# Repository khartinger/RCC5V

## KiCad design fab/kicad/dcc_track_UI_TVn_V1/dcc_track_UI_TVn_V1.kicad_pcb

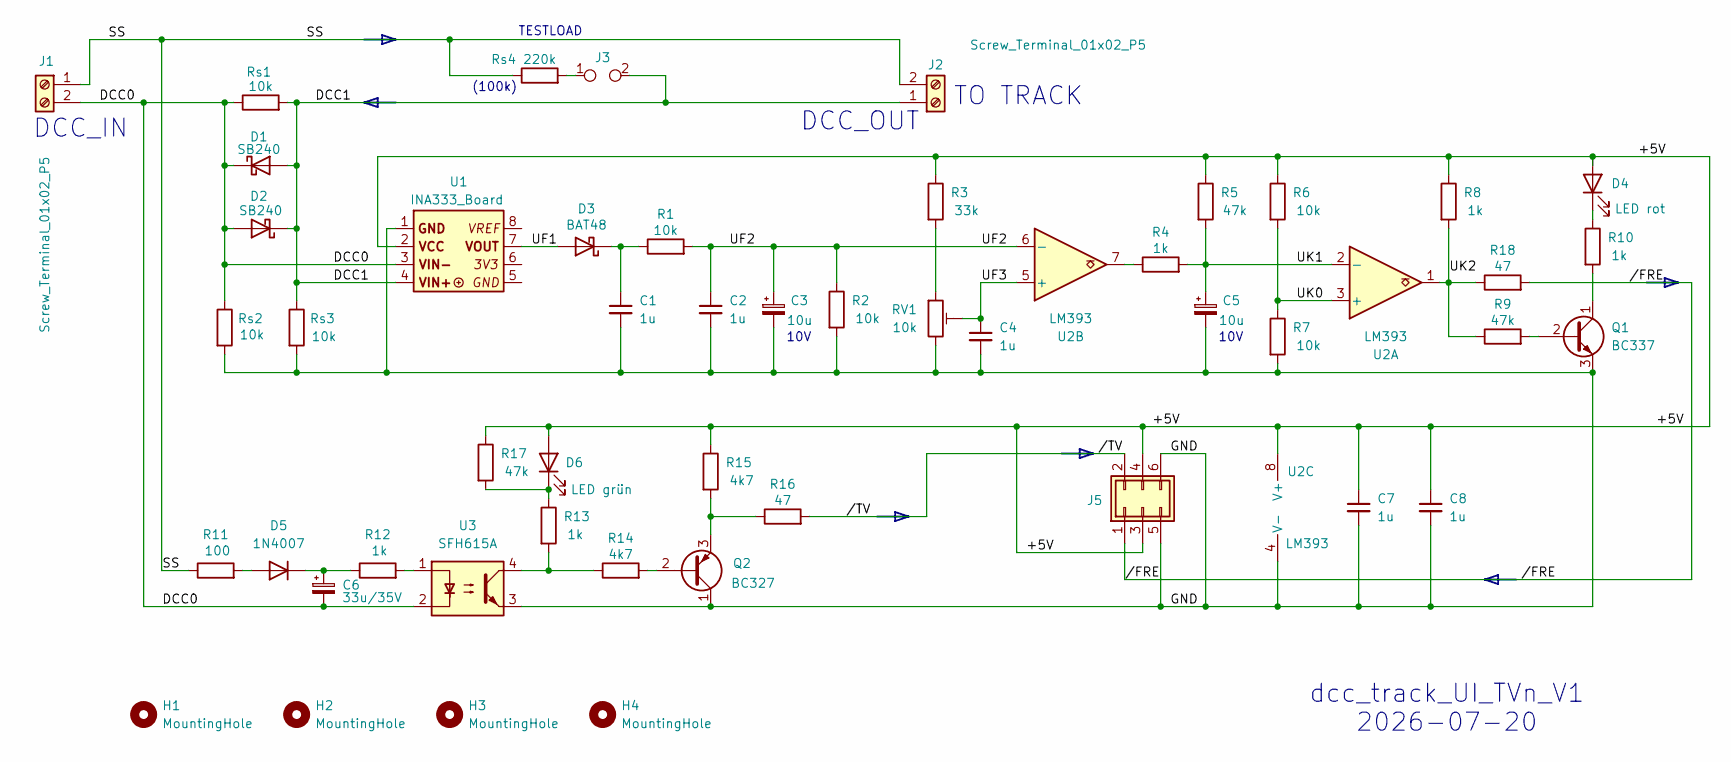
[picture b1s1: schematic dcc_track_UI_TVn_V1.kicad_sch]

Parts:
C1, C2, C4, C7, C8: 1u; C_L4mm_D3mm_P2.54mm_kh
C3, C5: 10u; ELKO_L4.32mm_D3.81mm_P2.54mm_kh
C6: 33u/35V; CP_Radial_D8.0mm_P2.50mm
D1, D2: SB240; D_DO-15_P3.81mm_Vertical_AnodeUp
D3: BAT48; D_DO-35_SOD27_P5.08mm_Horizontal_kh
D4: LED rot; LED_D3.0mm
D5: 1N4007; D_DO-41_SOD81_P3.81mm_Vertical_AnodeUp_kh
D6: LED grün; LED_D3.0mm
H1, H2, H3, H4: MountingHole; MountingHole_2.2mm_M2_Pad_TopBottom_kh
J1, J2: Screw_Terminal_01x02_P5
J3: Jumper_2; PinSocket_1x02_P2.54mm_Vertical_kh
J5: Box_02x03_P2.54_Vertical; Box_02x03_P2.54mm_Vertical_kh
Q1: BC337; TO-92_Inline_Wide_custom
Q2: BC327; TO-92_Inline_Wide_custom
R1: 10k; R_Axial_DIN0204_L3.6mm_D1.6mm_P7.62mm_Horizontal
R2, R6, R7: 10k; R_Axial_DIN0204_L3.6mm_D1.6mm_P2.54mm_Vertical_kh
R3: 33k; R_Axial_DIN0204_L3.6mm_D1.6mm_P2.54mm_Vertical_kh
R4, R8, R10, R12, R13: 1k; R_Axial_DIN0204_L3.6mm_D1.6mm_P2.54mm_Vertical_kh
R5: 47k; R_Axial_DIN0204_L3.6mm_D1.6mm_P7.62mm_Horizontal
R9, R17: 47k; R_Axial_DIN0204_L3.6mm_D1.6mm_P2.54mm_Vertical_kh
R11: 100; R_Axial_DIN0204_L3.6mm_D1.6mm_P2.54mm_Vertical
R14, R15: 4k7; R_Axial_DIN0204_L3.6mm_D1.6mm_P2.54mm_Vertical_kh
R16, R18: 47; R_Axial_DIN0204_L3.6mm_D1.6mm_P2.54mm_Vertical_kh
RV1: 10k; Trim_Bourns_3296W_Vertical
Rs1: 10k; R_Axial_DIN0204_L3.6mm_D1.6mm_P2.54mm_Vertical_kh
Rs2, Rs3: 10k; R_Axial_DIN0204_L3.6mm_D1.6mm_P7.62mm_Horizontal
Rs4: 220k; R_Axial_DIN0204_L3.6mm_D1.6mm_P7.62mm_Horizontal
U1: INA333_Board
U2: LM393; DIP-8_W7.62mm_Socket_LongPads
U3: SFH615A; DIP-4_W7.62mm

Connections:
/+5V: C7.1, C8.1, D4.2 (A), D6.2 (A), J5.3, J5.4, R3.1, R5.1, R6.1, R8.1, R15.1, R17.1, U1.2 (3A), U2.8 (V+)
/DCC0: C6.2, D1.1 (K), D2.2 (A), J1.2, Rs1.1, Rs2.1, U1.3, U3.2
/DCC1: D1.2 (A), D2.1 (K), J2.1, J3.2, Rs1.2, Rs3.1, U1.4 (PIN_4)
/GND: C1.2, C2.2, C3.2, C4.2, C5.2, C7.2, C8.2, J5.5, J5.6, Q1.3 (E), Q2.1 (C), R2.2, R7.2, RV1.3, Rs2.2, Rs3.2, U1.1, U2.4 (V-), U3.3
/SS: J1.1, J2.2, R11.1, Rs4.1
/UF1: D3.2 (A), U1.7
/UF2: C2.1, C3.1, R1.2, R2.1, U2.6 (-)
/UF3: C4.1, RV1.2, U2.5 (+)
/UK0: R6.2, R7.1, U2.3 (+)
/UK1: C5.1, R4.2, R5.2, U2.2 (-)
/UK2: R8.2, R9.1, R18.1, U2.1
//FRE: J5.1, R18.2
//TV: J5.2, R16.2
unnamed: C1.1, D3.1 (K), R1.1
unnamed: D4.1 (K), R10.1
unnamed: D5.2 (A), R11.2
unnamed: C6.1, D5.1 (K), R12.1
unnamed: D6.1 (K), R13.1, R17.2
unnamed: J3.1, Rs4.2
unnamed: Q1.2 (B), R9.2
unnamed: Q1.1 (C), R10.2
unnamed: Q2.2 (B), R14.2
unnamed: Q2.3 (E), R15.2, R16.1
unnamed: R3.2, RV1.1
unnamed: R4.1, U2.7
unnamed: R12.2, U3.1
unnamed: R13.2, R14.1, U3.4

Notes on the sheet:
dcc_track_UI_TVn_V1 2026-07-20
10V
DCC_OUT
TESTLOAD
TO TRACK
(100k)
DCC_IN

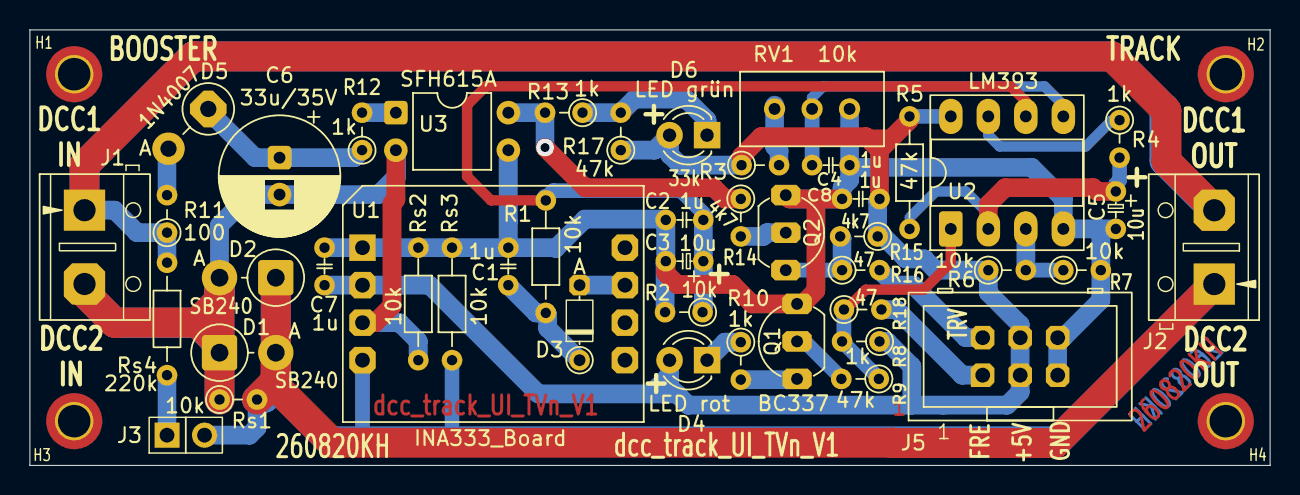
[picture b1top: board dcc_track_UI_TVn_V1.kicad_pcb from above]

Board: 2 copper layers, 84.0 x 29.5 mm, 50 parts (0 on the bottom side), 27 nets.

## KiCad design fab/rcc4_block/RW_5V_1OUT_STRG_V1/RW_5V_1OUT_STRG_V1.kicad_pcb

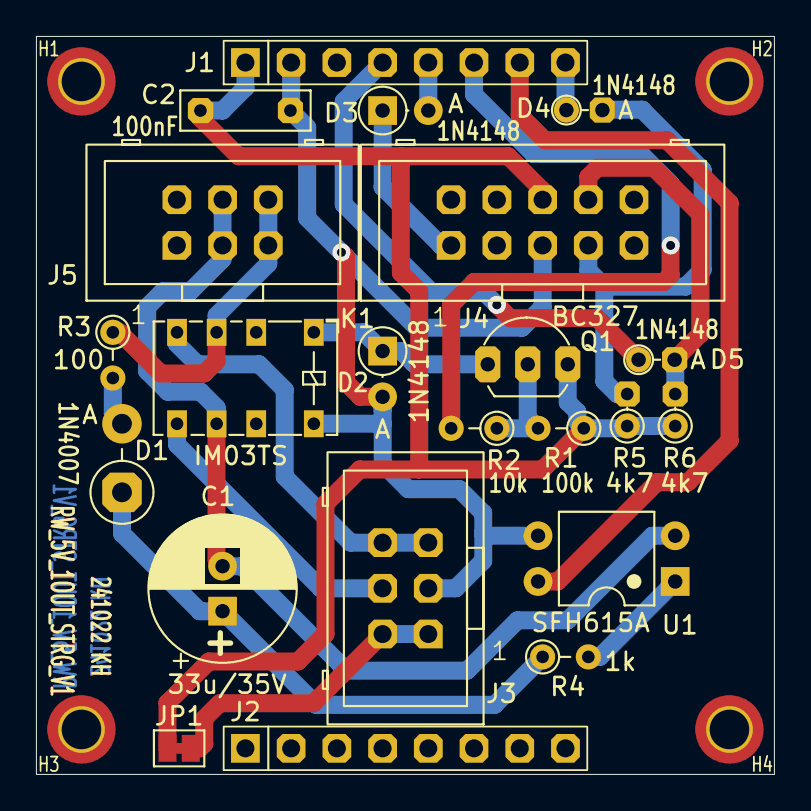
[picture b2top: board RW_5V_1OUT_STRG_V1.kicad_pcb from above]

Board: 2 copper layers, 41.0 x 41.0 mm, 26 parts (0 on the bottom side), 20 nets.

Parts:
C1: 33u/35V; CP_Radial_D8.0mm_P2.50mm
C2: 100nF; C_Rect_L7.0mm_W2.0mm_P5.00mm_kh
D1: 1N4007; D_DO-41_SOD81_P3.81mm_Vertical_AnodeUp_kh
D2, D3: 1N4148; D_DO-35_SOD27_P2.54mm_Vertical_AnodeUp
D4, D5: 1N4148; D_DO-35_P2.0mm_Vertical_AnodeUp_kh
H1, H2, H3, H4: MountingHole; MountingHole_2.2mm_M2_Pad_TopBottom_kh
J1, J2: Conn_01x08_Pin; PinSocket_1x08_P2.54mm_Vertical_kh
J3, J5: Box_02x03_P2.54_Vertical; Box_02x03_P2.54mm_Vertical_kh
J4: Box_02x05_P2.54_Vertical; Box_02x05_P2.54mm_Vertical_kh
JP1: Jumper_2_Bridged; SolderJumper-2_P1.3mm_Bridged_Pad1.0x1.5mm
K1: IM03TS; Relay_DPDT_AXICOM_IMSeries_Pitch5.08mm_rect_Pins
Q1: BC327; TO-92_Inline_Wide_2.2225
R1: 100k; R_Axial_DIN0204_L3.6mm_D1.6mm_P2.54mm_Vertical
R2: 10k; R_Axial_DIN0204_L3.6mm_D1.6mm_P2.54mm_Vertical
R3: 100; R_Axial_DIN0204_L3.6mm_D1.6mm_P2.54mm_Vertical
R4: 1k; R_Axial_DIN0204_L3.6mm_D1.6mm_P2.54mm_Vertical
R5, R6: 4k7; R_Axial_P1.778mm_Vertical_kh
U1: SFH615A; DIP-4_W7.62mm

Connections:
/0V: C2.1, D2.2 (A), J1.2, J3.3, J4.5, K1.8, U1.3
/5V: J3.1, J3.2, JP1.2 (B)
/OUT+: J5.5, J5.6, K1.3, R3.1
/OUT-: C1.2, J5.3, J5.4, K1.6, U1.2
/Q1B: Q1.2 (B), R1.2, R2.1
/R0: J1.7, U1.4
/R1: D4.2 (A), J4.7, R5.2
/R1i: D4.1 (K), J1.8
/R2: D5.2 (A), J4.8, R6.2
/R2i: D5.1 (K), J1.4
/REL+: D2.1 (K), K1.1, Q1.1 (C)
/S0: J1.6, R2.2
/S1: D3.1 (K), J4.1
/S1i: D3.2 (A), J1.5
/V+: J3.5, J3.6, K1.4
/V-: J3.4, K1.5
/V_I2C: C2.2, J1.1, J4.6, JP1.1 (A), Q1.3 (E), R1.1, R5.1, R6.1
unnamed: D1.2 (A), R3.2
unnamed: C1.1, D1.1 (K), R4.1
unnamed: R4.2, U1.1

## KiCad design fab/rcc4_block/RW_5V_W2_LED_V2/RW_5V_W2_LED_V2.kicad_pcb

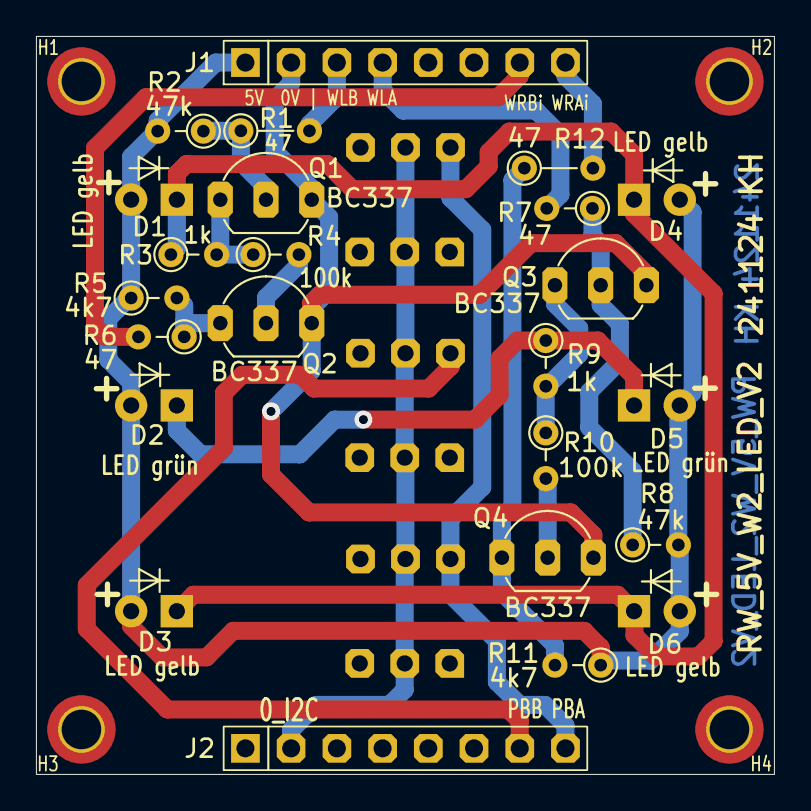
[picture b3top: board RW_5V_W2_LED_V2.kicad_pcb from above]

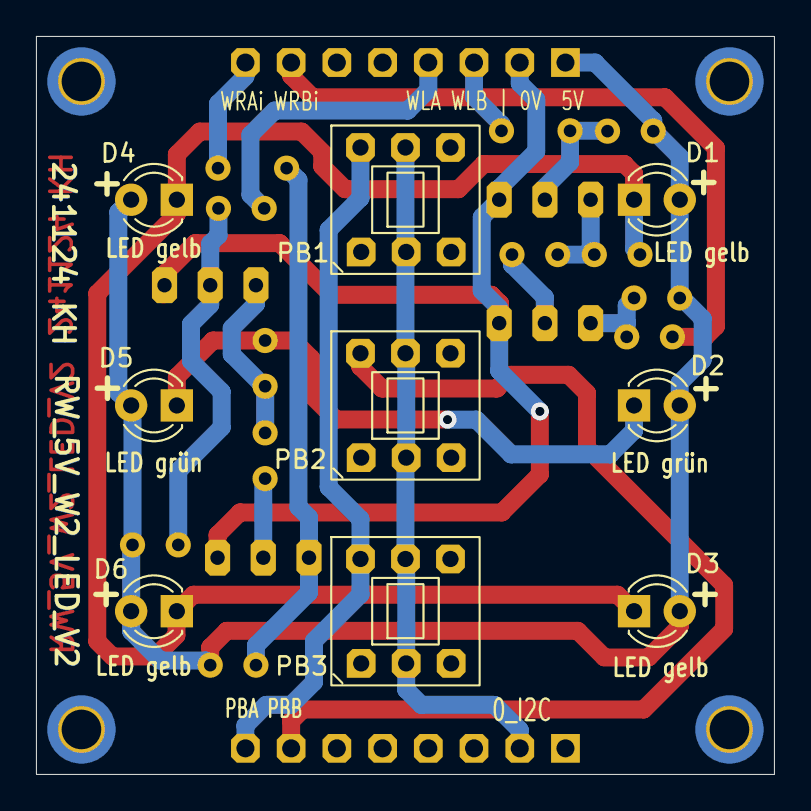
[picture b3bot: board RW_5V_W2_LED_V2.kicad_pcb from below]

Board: 2 copper layers, 41.0 x 41.0 mm, 31 parts (9 on the bottom side), 19 nets.

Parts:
D1, D3, D4, D6: LED gelb; LED_D3.0mm
D2, D5: LED grün; LED_D3.0mm
H1, H2, H3, H4: MountingHole; MountingHole_2.2mm_M2_Pad_TopBottom_kh
J1, J2: Conn_01x08_Pin; PinSocket_1x08_P2.54mm_Vertical_kh
PB1, PB2, PB3: SW_Push_DPDT_8x8
Q1, Q2, Q3, Q4: BC337; TO-92_Inline_Wide_custom
R1, R12: 47; R_Axial_DIN0204_L3.6mm_D1.6mm_P3.81mm_Vertical_kh
R2, R8: 47k; R_Axial_DIN0204_L3.6mm_D1.6mm_P2.54mm_Vertical
R3, R9: 1k; R_Axial_DIN0204_L3.6mm_D1.6mm_P2.54mm_Vertical
R4: 100k; R_Axial_DIN0204_L3.6mm_D1.6mm_P2.54mm_Vertical
R5, R11: 4k7; R_Axial_DIN0204_L3.6mm_D1.6mm_P2.54mm_Vertical
R6: 47; R_Axial_DIN0204_L3.6mm_D1.6mm_P2.54mm_Vertical
R7: 47; R_Axial_DIN0204_L3.6mm_D1.6mm_P2.54mm_Vertical_kh
R10: 100k; R_Axial_DIN0204_L3.6mm_D1.6mm_P2.54mm_Vertical_kh

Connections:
/0V: J1.2, Q1.3 (E), Q2.3 (E), Q3.3 (E), Q4.3 (E)
/0_I2C: J2.2, PB1.2 (B), PB1.5 (B), PB2.2 (B), PB2.5 (B), PB3.2 (B), PB3.5 (B)
/+5V: D1.2 (A), D2.2 (A), D3.2 (A), D4.2 (A), D5.2 (A), D6.2 (A), J1.1, R2.2, R5.1, R8.2, R11.1
/PBA: J2.8, PB1.6 (C), PB3.6 (C)
/PBB: J2.7, PB2.6 (C)
/WLA: J1.4, R7.2
/WLB: J1.3, R1.2
/WRAi: J1.8, R12.2
/WRBi: J1.7, R6.2
unnamed: D1.1 (K), D3.1 (K), D4.1 (K), D6.1 (K), R3.1
unnamed: D2.1 (K), D5.1 (K), R9.1
unnamed: Q1.2 (B), R1.1, R2.1
unnamed: Q1.1 (C), R3.2, R4.1
unnamed: Q2.2 (B), R4.2
unnamed: Q2.1 (C), R5.2, R6.1
unnamed: Q3.2 (B), R7.1, R8.1
unnamed: Q3.1 (C), R9.2, R10.1
unnamed: Q4.2 (B), R10.2
unnamed: Q4.1 (C), R11.2, R12.1

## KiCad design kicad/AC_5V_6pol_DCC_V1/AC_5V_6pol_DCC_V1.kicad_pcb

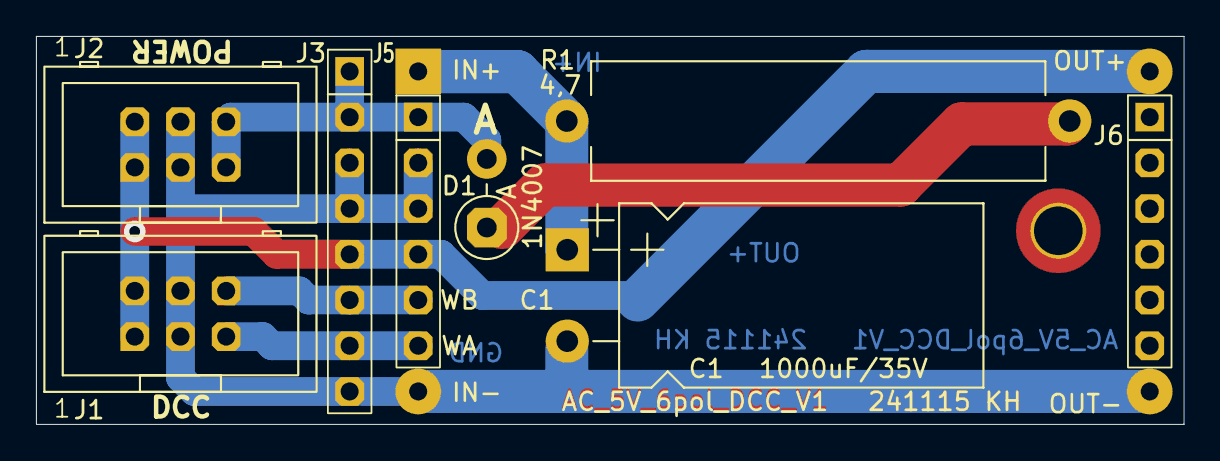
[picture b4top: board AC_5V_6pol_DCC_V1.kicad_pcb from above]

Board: 2 copper layers, 63.8 x 21.6 mm, 10 parts (0 on the bottom side), 7 nets.

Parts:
C1: 1000uF/35V; CP_Radial_L20.0mm_D10.0mm_P5.08mm_Horizontal
D1: 1N4007; D_DO-41_SOD81_P3.81mm_Vertical_AnodeUp_kh
H1: MountingHole; MountingHole_2.7mm_M2.5_DIN965_Pad_TopBottom
J1: Box_02x03_P2.54_Vertical; Box_02x03_P2.54mm_Vertical_kh
J2: Box_02x03_P2.54_Vertical_kh; Box_02x03_P2.54mm_Vertical_kh
J3: Conn_01x08; PinSocket_1x08_P2.54mm_Vertical_kh
J5, J6: Conn_01x06; PinSocket_1x06_P2.54mm_Vertical_kh
R1: 4,7; R_Axial_Power_L25.0mm_W6.4mm_P27.94mm
U1: DCDC_StepDown_LM2596; DCDC_StepDown_LM2596_PinsOnly

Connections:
/5V: J1.1, J1.2, J2.1, J2.2, J3.5, J5.4, U1.4 (Vout)
/AC+: D1.2 (A), J2.5, J2.6, J3.1, J3.2, J5.1
/AC-: C1.2, J1.3, J1.4, J2.3, J2.4, J3.3, J3.4, J3.8, J5.2, J5.3, U1.2 (GND), U1.3 (GND)
/IN+: C1.1, R1.1, U1.1 (Vin)
/WA: J1.5, J3.7, J5.6
/WB: J1.6, J3.6, J5.5
unnamed: D1.1 (K), R1.2

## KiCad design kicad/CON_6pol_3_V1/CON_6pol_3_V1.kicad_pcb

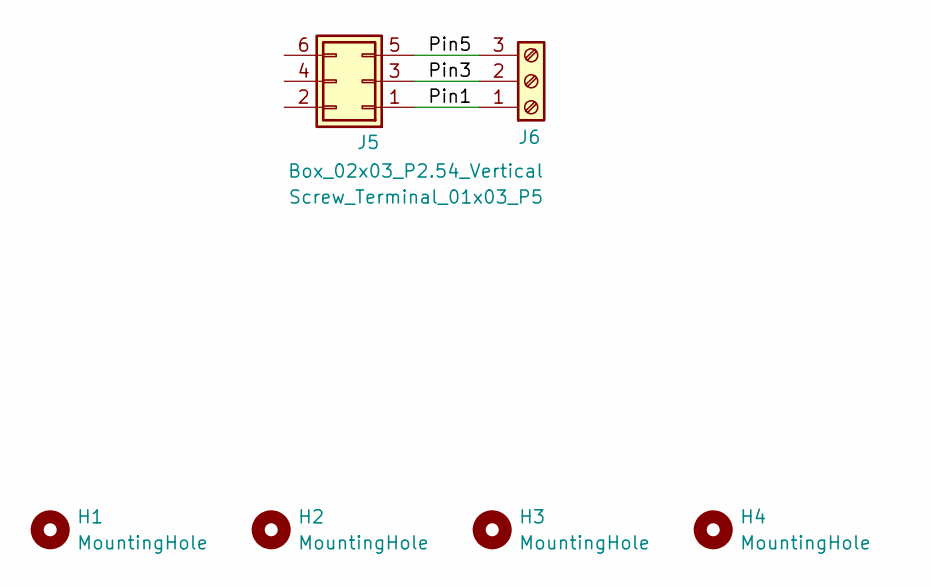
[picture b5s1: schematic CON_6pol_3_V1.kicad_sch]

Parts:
H1, H2, H3, H4: MountingHole; MountingHole_2.2mm_M2_Pad_TopBottom_kh
J5: Box_02x03_P2.54_Vertical; Box_02x03_P2.54mm_Vertical_kh
J6: Screw_Terminal_01x03_P5

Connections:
/Pin1: J5.1, J6.1
/Pin3: J5.3, J6.2
/Pin5: J5.5, J6.3

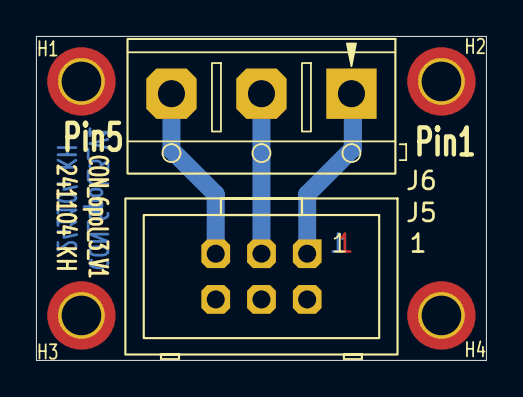
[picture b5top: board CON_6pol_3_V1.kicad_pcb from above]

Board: 2 copper layers, 25.0 x 18.0 mm, 6 parts (0 on the bottom side), 3 nets.
